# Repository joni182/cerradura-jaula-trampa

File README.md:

# Proyecto de cierre para jaula trampa para protectoras

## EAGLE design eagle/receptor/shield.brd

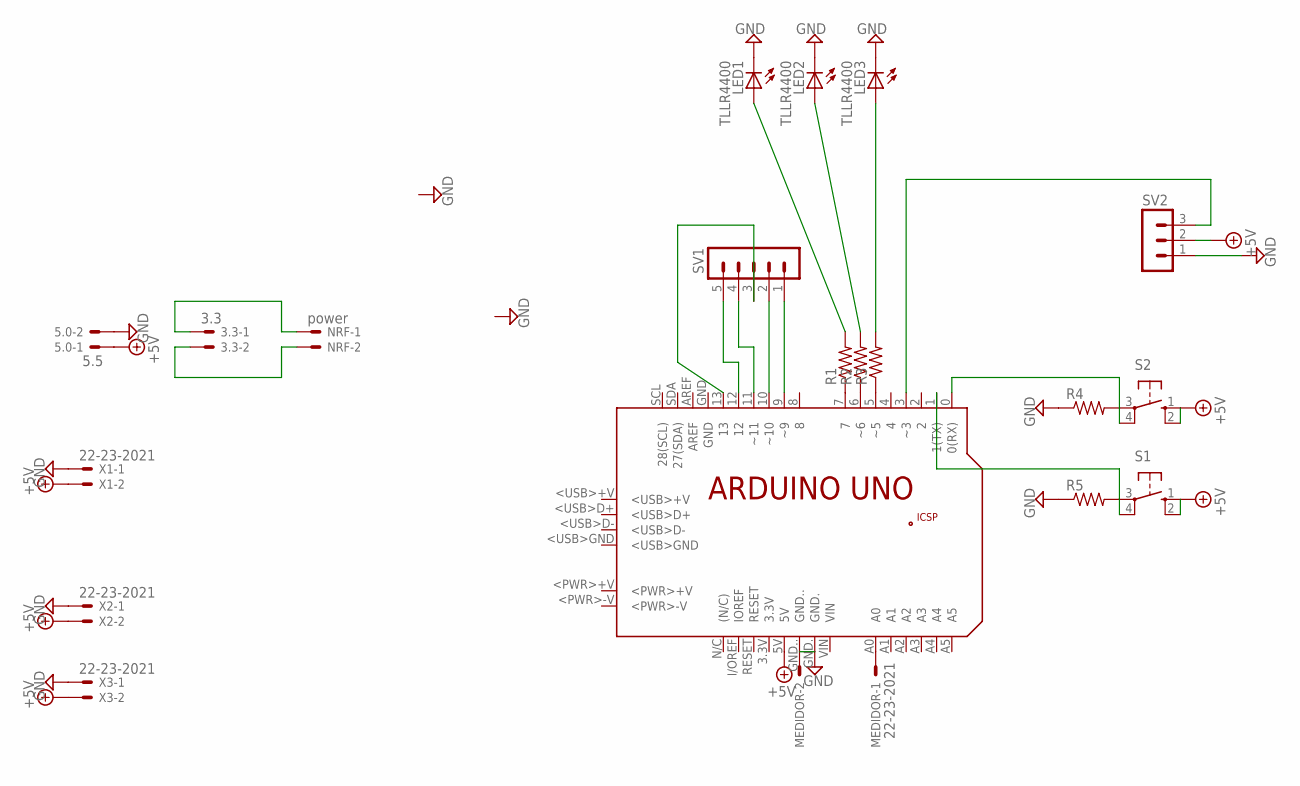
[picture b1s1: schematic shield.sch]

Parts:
3.3: 3.3; 22-23-2021
5.0: 5.5; 22-23-2021
LED1, LED2, LED3: TLLR4400; LED3MM
MEDIDOR: 22-23-2021
NRF: power; 22-23-2021
PCB1: ARDUINO_UNO
R1, R2, R3, R4, R5: R-US_0613/15; P0613/15
S1, S2: 10-XX; B3F-10XX
SV1: MA05-1
SV2: MA03-1
X1, X2, X3: 22-23-2021

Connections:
+5V: 5.0.1, PCB1.5V, S1.1 (S), S1.2 (S1), S2.1 (S), S2.2 (S1), SV2.2, X1.2, X2.2, X3.2
GND: 5.0.2, LED1.K (C), LED2.K (C), LED3.K (C), MEDIDOR.2, PCB1.GND., PCB1.GND.., R4.1, R5.1, SV2.1, X1.1, X2.1, X3.1
unnamed: PCB1.3 (~3), SV2.3
unnamed: PCB1.9 (~9), SV1.1
unnamed: PCB1.10 (~10), SV1.2
unnamed: PCB1.13, SV1.3
unnamed: PCB1.11 (~11), SV1.4
unnamed: PCB1.12, SV1.5
unnamed: PCB1.0 (0(RX)), R4.2, S2.3, S2.4 (P1)
unnamed: PCB1.7, R1.1
unnamed: PCB1.6 (~6), R2.1
unnamed: PCB1.5 (~5), R3.1
unnamed: LED3.A, R3.2
unnamed: LED2.A, R2.2
unnamed: LED1.A, R1.2
unnamed: PCB1.1 (1(TX)), R5.2, S1.3, S1.4 (P1)
unnamed: MEDIDOR.1, PCB1.A0
unnamed: 3.3.1, NRF.1
unnamed: 3.3.2, NRF.2

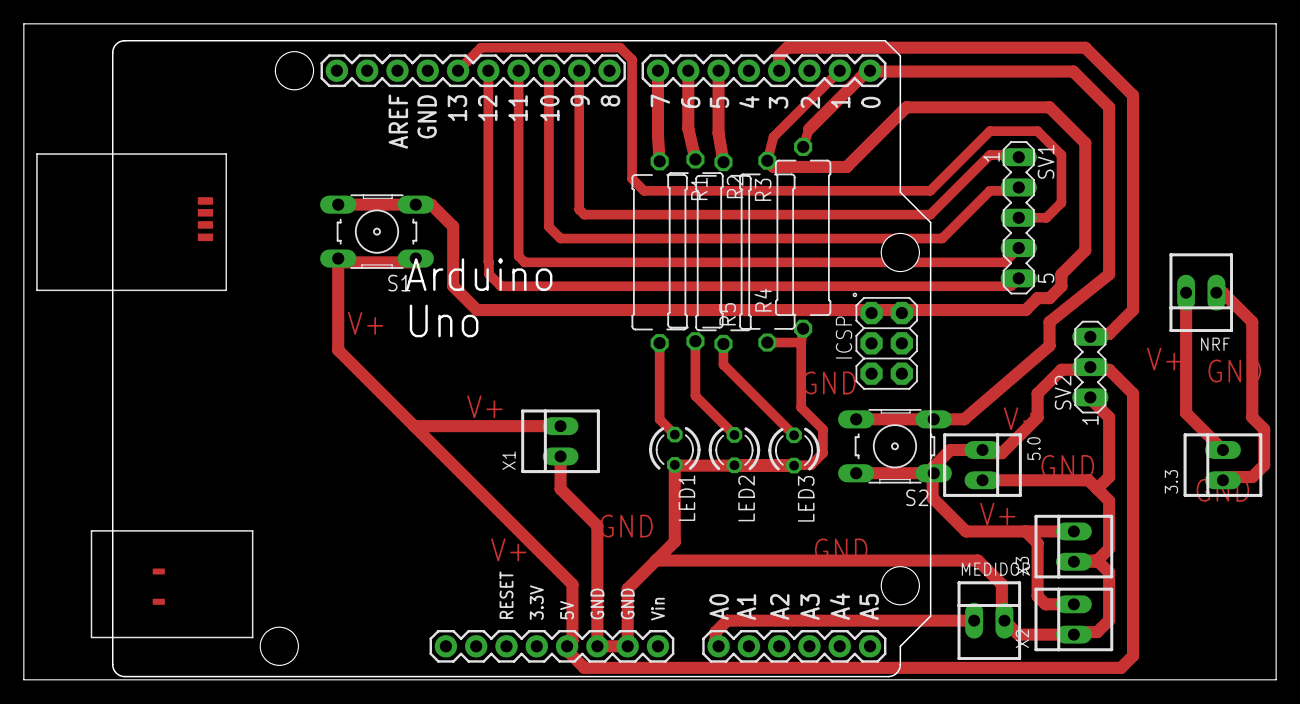
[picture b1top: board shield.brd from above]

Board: 2 copper layers, 105.0 x 55.0 mm, 20 parts (0 on the bottom side), 19 nets.

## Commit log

2018-09-03 Carga inicial
2018-09-03 configurado tres pulsadores
2018-09-03 Pruebas receptor
2018-09-03 El motor se controla a distancia
2018-09-04 prototipo de mando empezado en fritzing
2018-10-03 Agregada archivos de eagle para la shield del receptor
2018-10-03 reestructurando carpetas
2018-10-03 Agregado readme
